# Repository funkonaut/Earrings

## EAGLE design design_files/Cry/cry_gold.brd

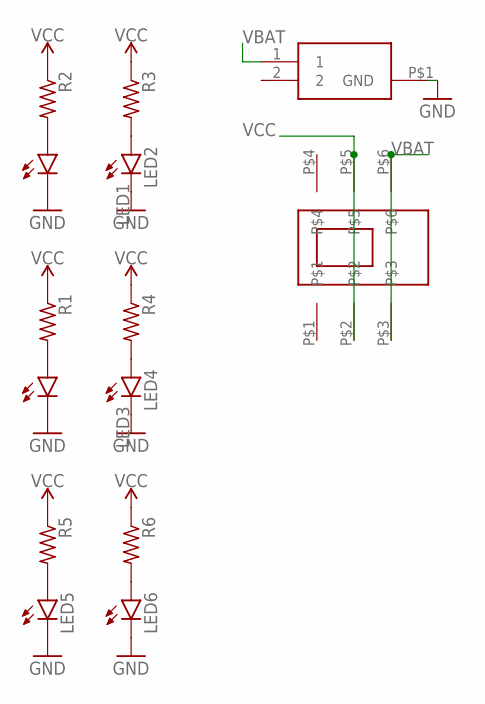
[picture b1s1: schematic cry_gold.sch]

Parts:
LED1, LED2, LED3, LED4, LED5, LED6: LEDCHIP-LED0805; CHIP-LED0805
R1, R2, R3, R4, R5, R6: R-US_R0603; R0603
U$1: CL-SB-22A-02T-SLIDE-SWITCH-TUCKED-PADS; CL-SB-22A-02T-DPDT-COMPACT-SWITCH
VBAT: BAT-HLD-012-SMT; BATHLD012SMT

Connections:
GND: LED1.C, LED2.C, LED3.C, LED4.C, LED5.C, LED6.C, VBAT.P$1 (GND)
unnamed: LED1.A, R2.2
unnamed: LED3.A, R1.2
unnamed: LED5.A, R5.2
unnamed: LED2.A, R3.2
unnamed: LED4.A, R4.2
unnamed: LED6.A, R6.2
VBAT: U$1.P$3, U$1.P$6, VBAT.1
VCC: R1.1, R2.1, R3.1, R4.1, R5.1, R6.1, U$1.P$2, U$1.P$5

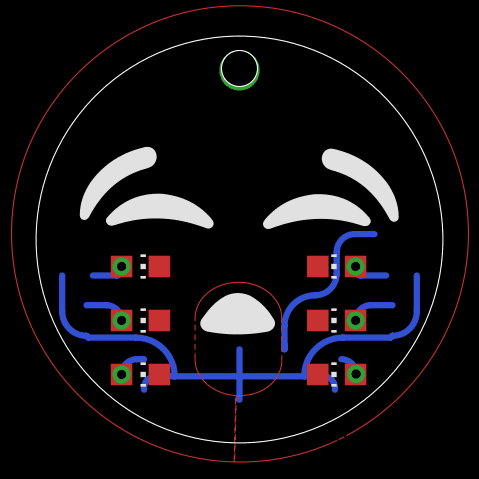
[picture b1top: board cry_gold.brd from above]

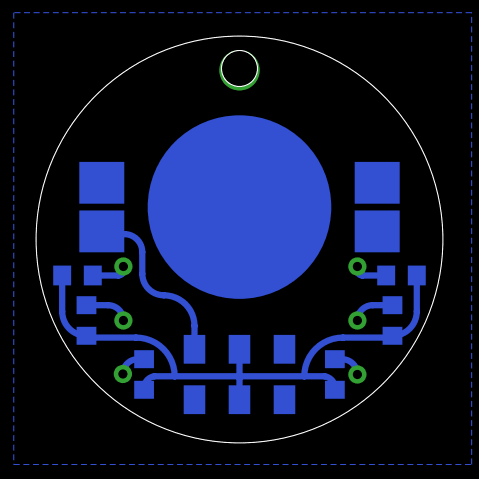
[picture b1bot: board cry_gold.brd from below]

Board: 2 copper layers, 22.6 x 22.6 mm, 14 parts (8 on the bottom side), 9 nets.

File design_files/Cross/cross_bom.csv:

Part,Value,Device,Package,Description,HEIGHT,MANUFACTURER_NAME,MANUFACTURER_PART_NUMBER,MOUSER_PART_NUMBER,MOUSER_PRICE-STOCK,POPULARITY,SPICEPREFIX,
LED1,,LEDCHIP-LED0805,CHIP-LED0805,LED,,,,,,68,,
LED2,,LEDCHIP-LED0805,CHIP-LED0805,LED,,,,,,68,,
LED3,,LEDCHIP-LED0805,CHIP-LED0805,LED,,,,,,68,,
LED4,,LEDCHIP-LED0805,CHIP-LED0805,LED,,,,,,68,,
R1,,R-US_R0603,R0603,"RESISTOR, American symbol",,,,,,77,R,
R2,,R-US_R0603,R0603,"RESISTOR, American symbol",,,,,,77,R,
R3,,R-US_R0603,R0603,"RESISTOR, American symbol",,,,,,77,R,
R4,,R-US_R0603,R0603,"RESISTOR, American symbol",,,,,,77,R,
U$1,CL-SB-22A-02T-SLIDE-SWITCH-TUCKED-PADS,CL-SB-22A-02T-SLIDE-SWITCH-TUCKED-PADS,CL-SB-22A-11T side setting,(names in device are wrong),,,,,,,,
VBAT,BAT-HLD-012-SMT,BAT-HLD-012-SMT,BATHLD012SMT,Coin Cell Battery Holders Bat Hld CR1216/1225 Surface Mount,3mm,Linx Technologies,BAT-HLD-012-SMT,712-BAT-HLD-012-SMT,https://www.mouser.com/Search/Refine.aspx?Keyword=712-BAT-HL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,,,

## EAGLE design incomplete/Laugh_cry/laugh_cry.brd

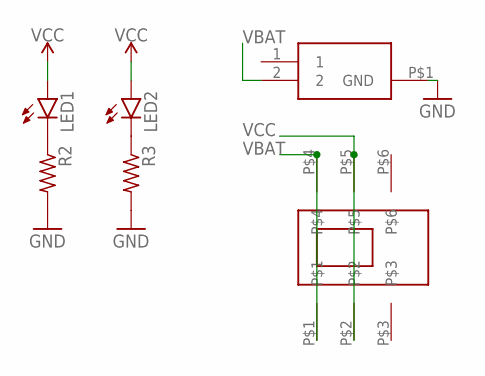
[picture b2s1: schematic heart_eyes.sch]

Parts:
LED1, LED2: LEDCHIP-LED0805; CHIP-LED0805
R2, R3: R-US_R0603; R0603
U$1: CL-SB-22A-02T-SLIDE-SWITCH-TUCKED-PADS; CL-SB-22A-02T-DPDT-COMPACT-SWITCH
VBAT: BAT-HLD-012-SMT; BATHLD012SMT

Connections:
GND: R2.2, R3.2, VBAT.P$1 (GND)
unnamed: LED1.C, R2.1
unnamed: LED2.C, R3.1
VBAT: U$1.P$1, U$1.P$4, VBAT.2
VCC: LED1.A, LED2.A, U$1.P$2, U$1.P$5

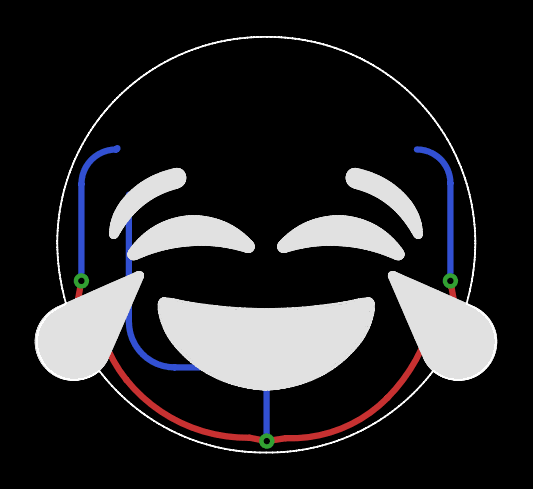
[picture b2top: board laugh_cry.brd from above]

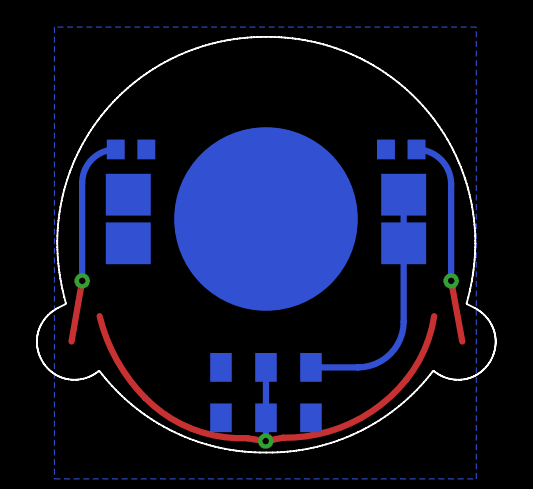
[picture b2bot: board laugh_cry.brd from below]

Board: 2 copper layers, 25.5 x 23.1 mm, 6 parts (4 on the bottom side), 5 nets.

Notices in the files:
parts and their libraries:
SparkFun-PowerSymbols: Licensing: Creative Commons ShareAlike 4.0 International - https://creativecommons.org/licenses/by-sa/4.0
